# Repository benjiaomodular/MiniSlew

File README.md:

# [WIP] MiniSlew

## License

This work is licensed under a
[Creative Commons Attribution-ShareAlike 4.0 International License][cc-by-sa].

[![CC BY-SA 4.0][cc-by-sa-image]][cc-by-sa]

[cc-by-sa]: http://creativecommons.org/licenses/by-sa/4.0/
[cc-by-sa-image]: https://licensebuttons.net/l/by-sa/4.0/88x31.png
[cc-by-sa-shield]: https://img.shields.io/badge/License-CC%20BY--SA%204.0-lightgrey.svg

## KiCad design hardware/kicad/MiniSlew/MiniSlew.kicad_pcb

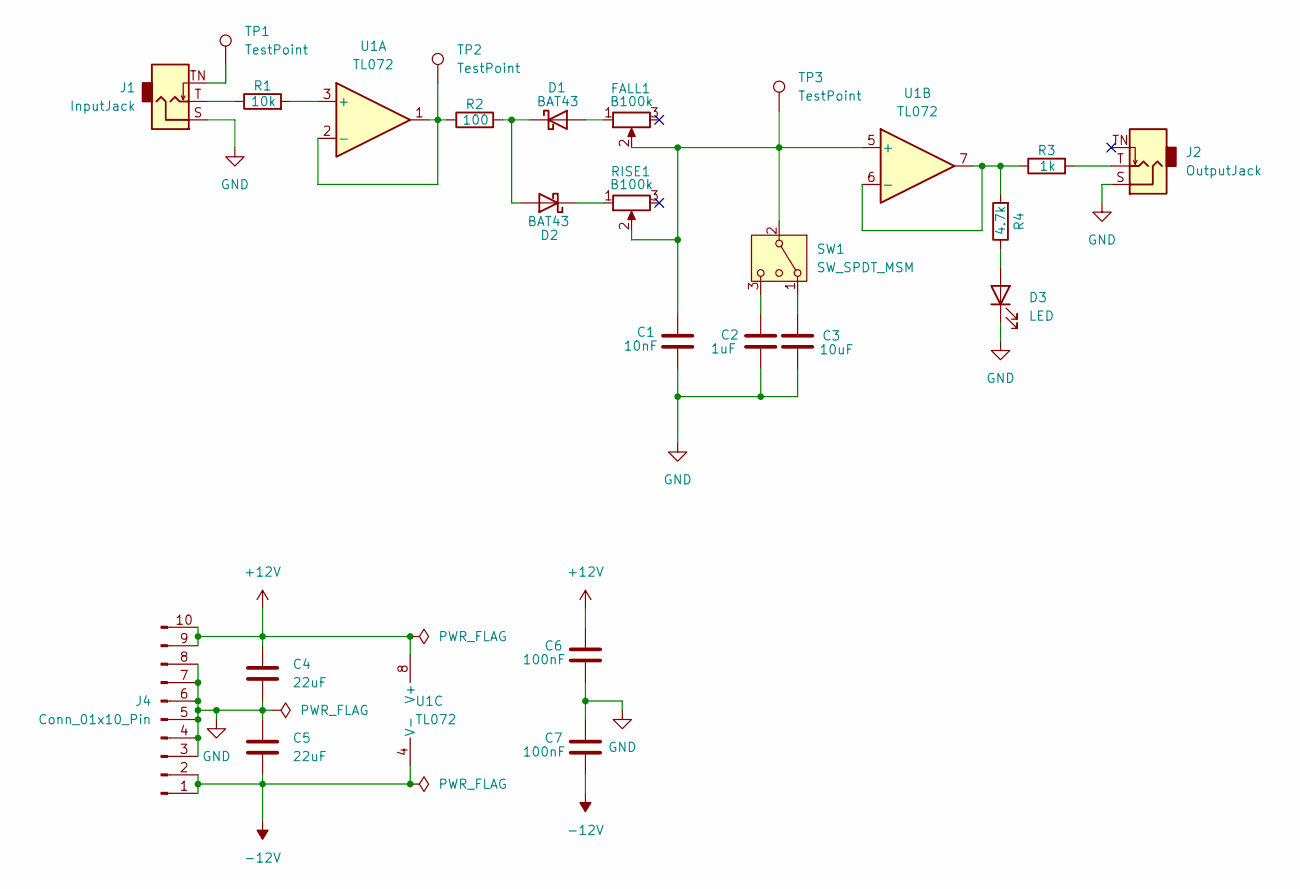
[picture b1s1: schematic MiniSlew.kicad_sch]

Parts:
C1: 10nF; C_0805_2012Metric_Pad1.18x1.45mm_HandSolder
C2: 1uF; CP_Elec_6.3x5.8
C3: 10uF; CP_Elec_6.3x5.8
C4, C5: 22uF; C_0805_2012Metric_Pad1.18x1.45mm_HandSolder; Manufacturers Part Numb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 GRM21BR61E226ME44L
C6, C7: 100nF; C_0805_2012Metric_Pad1.18x1.45mm_HandSolder
D1, D2: BAT43; D_SOD-123
D3: LED; LED_D3.0mm
FALL1: B100k; Potentiometer_RV09
J1: InputJack; AudioJack_3.5mm
J2: OutputJack; AudioJack_3.5mm
J4: Conn_01x10_Pin; IDC-Header_2x05_P2.54mm_Vertical
R1: 10k; R_0603_1608Metric
R2: 100; R_0603_1608Metric
R3: 1k; R_0603_1608Metric
R4: 4.7k; R_0603_1608Metric
RISE1: B100k; Potentiometer_RV09
SW1: SW_SPDT_MSM; ToggleSwitch_SMTS-102
TP1, TP2, TP3: TestPoint; SolderWirePad_1x01_SMD_1x2mm
U1: TL072; SOIC-8_3.9x4.9mm_P1.27mm

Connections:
+12V: C4.1, C6.1, J4.9, J4.10, U1.8 (V+)
-12V: C5.2, C7.2, J4.1, J4.2, U1.4 (V-)
GND: C1.2, C2.1, C3.2, C4.2, C5.1, C6.2, C7.1, D3.1 (K), J1.S, J2.S, J4.3, J4.4, J4.5, J4.6, J4.7, J4.8
unnamed: C3.1, SW1.1
unnamed: D1.2 (A), FALL1.1
unnamed: D1.1 (K), D2.2 (A), R2.2
unnamed: D2.1 (K), RISE1.1
unnamed: D3.2 (A), R4.1
unnamed: J1.T, R1.1
unnamed: J1.TN, TP1.1
unnamed: J2.T, R3.2
unnamed: C1.1, FALL1.2, RISE1.2, SW1.2 (3), TP3.1, U1.5 (+)
unnamed: C2.2, SW1.3 (4)
unnamed: R1.2, U1.3 (+)
unnamed: R2.1, TP2.1, U1.1, U1.2 (-)
unnamed: R3.1, R4.2, U1.6 (-), U1.7

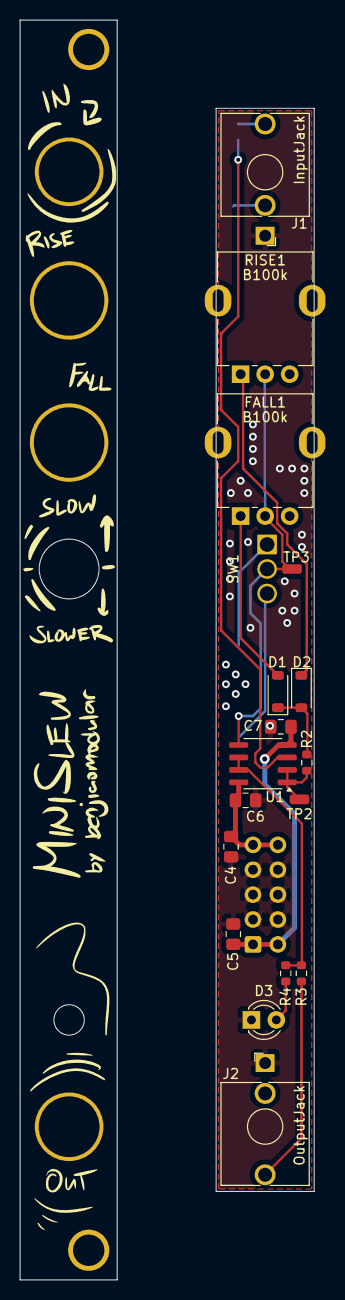
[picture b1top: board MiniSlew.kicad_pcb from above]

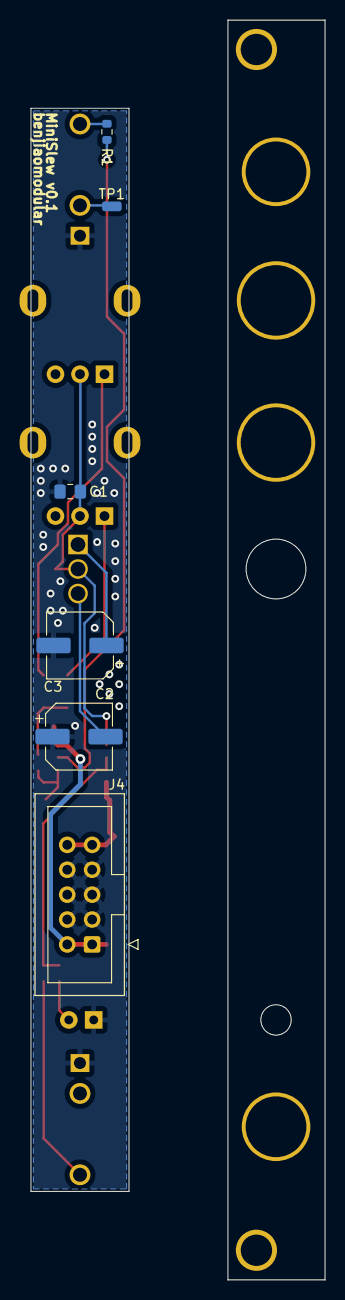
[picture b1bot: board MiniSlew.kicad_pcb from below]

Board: 2 copper layers, 10.0 x 110.5 mm, 24 parts (6 on the bottom side), 16 nets.

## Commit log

2024-06-06 initial release
2024-06-06 cleanup
2024-06-06 Added openscad panel
2024-09-09 v0.1 PCB ready for printing
